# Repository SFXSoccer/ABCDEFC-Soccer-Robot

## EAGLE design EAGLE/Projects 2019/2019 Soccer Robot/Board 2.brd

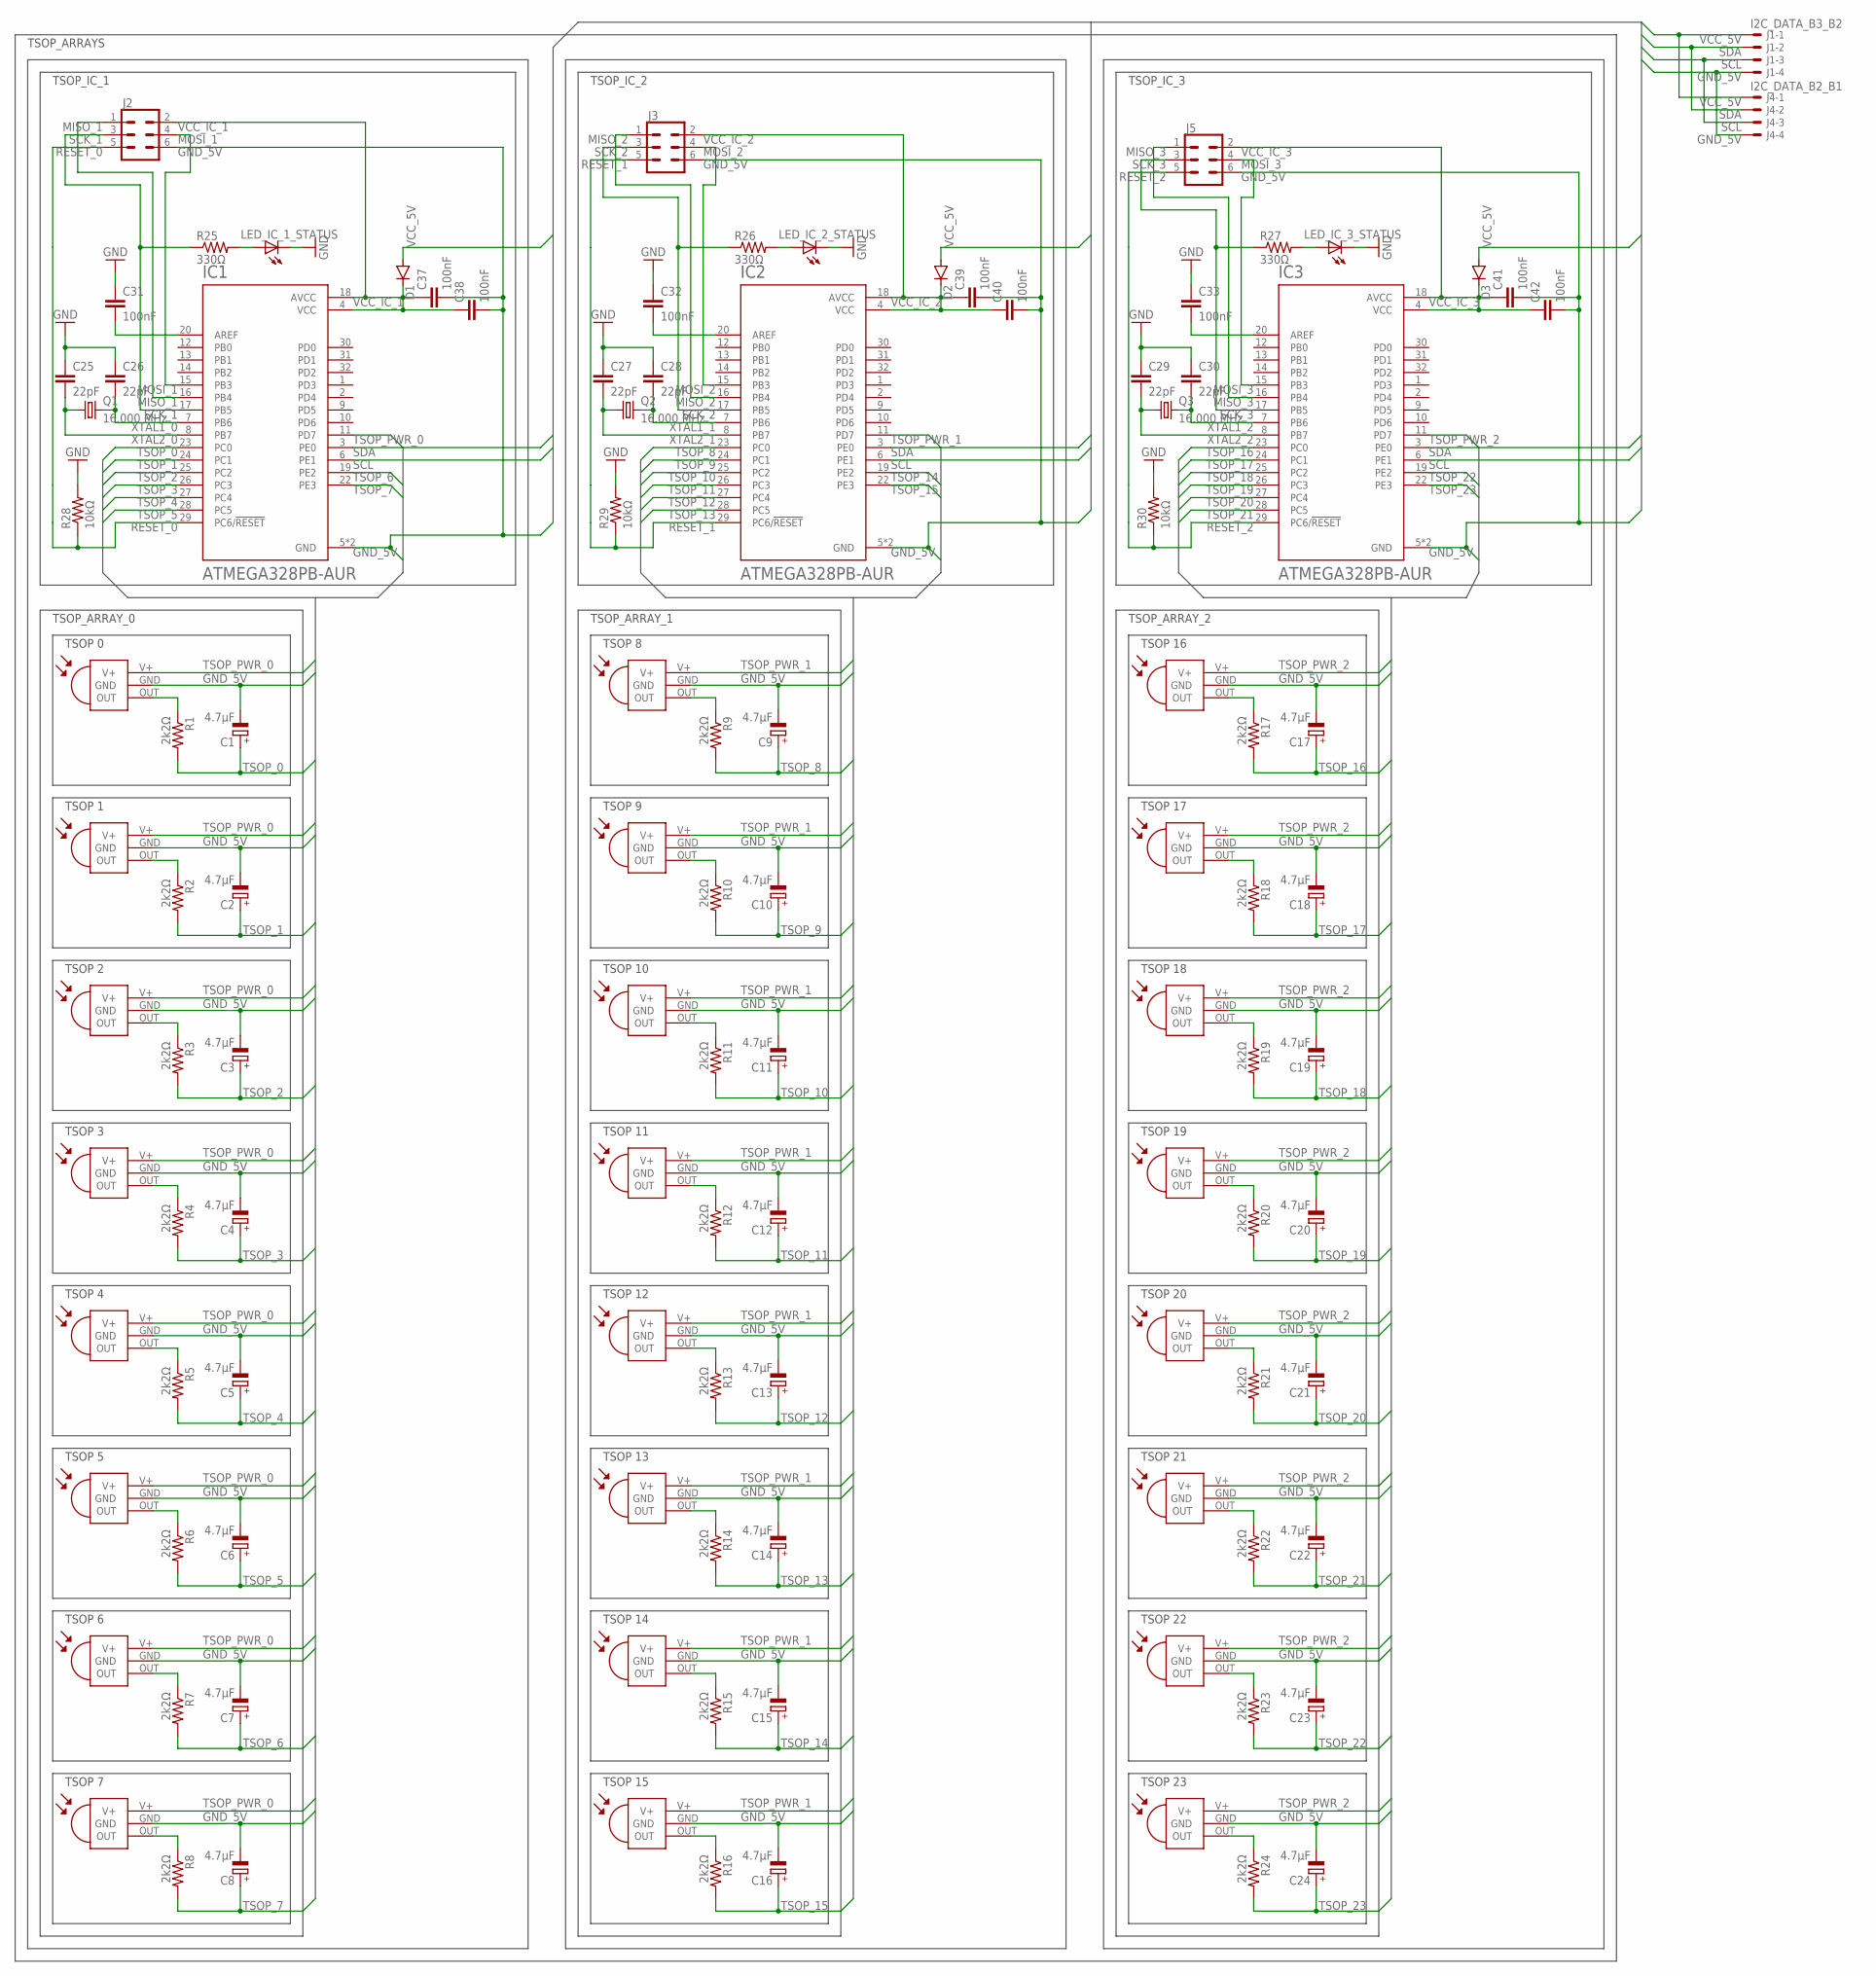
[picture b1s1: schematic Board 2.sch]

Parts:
C1, C2, C3, C4, C5, C6, C7, C8, C9, C10, C11, C12, C13, C14, C15, C16, C17, C18, C19, C20, C21, C22, C23, C24: 4.7µF; E2-5
C25, C26, C27, C28, C29, C30: 22pF; C050-024X044
C31, C32, C33, C37, C38, C39, C40, C41, C42: 100nF; C050-024X044
D1, D2, D3: 1N4148DO35-7; DO35-7
IC1, IC2, IC3: ATMEGA328PB-AUR; QFP80P900X900X120-32N
J1: I2C_DATA_B3_B2; 6410-04
J2, J3, J5: CONN_03X2SHROUD; 2X3-SHROUDED
J4: I2C_DATA_B2_B1; 6410-04
LED_IC_1_STATUS, LED_IC_2_STATUS, LED_IC_3_STATUS: LEDP-LCC-2; P-LCC-2
Q1, Q2, Q3: 16.000 MHz; HC49U-V
R1, R2, R3, R4, R5, R6, R7, R8, R9, R10, R11, R12, R13, R14, R15, R16, R17, R18, R19, R20, R21, R22, R23, R24: 2k2Ω; 0207/10
R25, R26, R27: 330Ω; 0207/10
R28, R29, R30: 10kΩ; 0207/10
TSOP_1, TSOP_2, TSOP_3, TSOP_4, TSOP_5, TSOP_6, TSOP_7, TSOP_8, TSOP_9, TSOP_10, TSOP_11, TSOP_12, TSOP_13, TSOP_14, TSOP_15, TSOP_16, TSOP_17, TSOP_18, TSOP_19, TSOP_20, TSOP_21, TSOP_22, TSOP_23, TSOP_24: TSOP14340; TSOP143XX

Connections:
GND_5V: C1.-, C2.-, C3.-, C4.-, C5.-, C6.-, C7.-, C8.-, C9.-, C10.-, C11.-, C12.-, C13.-, C14.-, C15.-, C16.-, C17.-, C18.-, C19.-, C20.-, C21.-, C22.-, C23.-, C24.-, C25.1, C26.1, C27.1, C28.1, C29.1, C30.1, C31.1, C32.1, C33.1, C37.2, C38.2, C39.2, C40.2, C41.2, C42.2, IC1.5 (GND), IC1.21 (GND), IC2.5 (GND), IC2.21 (GND), IC3.5 (GND), IC3.21 (GND), J1.4, J2.6, J3.6, J4.4, J5.6, LED_IC_1_STATUS.C, LED_IC_2_STATUS.C, LED_IC_3_STATUS.C, R28.2, R29.2, R30.2, TSOP_1.GND, TSOP_2.GND, TSOP_3.GND, TSOP_4.GND, TSOP_5.GND, TSOP_6.GND, TSOP_7.GND, TSOP_8.GND, TSOP_9.GND, TSOP_10.GND, TSOP_11.GND, TSOP_12.GND, TSOP_13.GND, TSOP_14.GND, TSOP_15.GND, TSOP_16.GND, TSOP_17.GND, TSOP_18.GND, TSOP_19.GND, TSOP_20.GND, TSOP_21.GND, TSOP_22.GND, TSOP_23.GND, TSOP_24.GND
MISO_1: IC1.16 (PB4), J2.1
MISO_2: IC2.16 (PB4), J3.1
MISO_3: IC3.16 (PB4), J5.1
MOSI_1: IC1.15 (PB3), J2.4
MOSI_2: IC2.15 (PB3), J3.4
MOSI_3: IC3.15 (PB3), J5.4
unnamed: R1.1, TSOP_1.OUT
unnamed: R2.1, TSOP_2.OUT
unnamed: R3.1, TSOP_3.OUT
unnamed: R4.1, TSOP_4.OUT
unnamed: R5.1, TSOP_5.OUT
unnamed: R6.1, TSOP_6.OUT
unnamed: R7.1, TSOP_7.OUT
unnamed: R8.1, TSOP_8.OUT
unnamed: R9.1, TSOP_9.OUT
unnamed: R10.1, TSOP_10.OUT
unnamed: R11.1, TSOP_11.OUT
unnamed: R12.1, TSOP_12.OUT
unnamed: R13.1, TSOP_13.OUT
unnamed: R14.1, TSOP_14.OUT
unnamed: R15.1, TSOP_15.OUT
unnamed: R16.1, TSOP_16.OUT
unnamed: R17.1, TSOP_17.OUT
unnamed: R18.1, TSOP_18.OUT
unnamed: R19.1, TSOP_19.OUT
unnamed: R20.1, TSOP_20.OUT
unnamed: R21.1, TSOP_21.OUT
unnamed: R22.1, TSOP_22.OUT
unnamed: R23.1, TSOP_23.OUT
unnamed: R24.1, TSOP_24.OUT
unnamed: LED_IC_1_STATUS.A, R25.2
unnamed: C31.2, IC1.20 (AREF)
unnamed: LED_IC_2_STATUS.A, R26.2
unnamed: C32.2, IC2.20 (AREF)
unnamed: LED_IC_3_STATUS.A, R27.2
unnamed: C33.2, IC3.20 (AREF)
RESET_0: IC1.29 (PC6/!RESET), J2.5, R28.1
RESET_1: IC2.29 (PC6/!RESET), J3.5, R29.1
RESET_2: IC3.29 (PC6/!RESET), J5.5, R30.1
SCK_1: IC1.17 (PB5), J2.3, R25.1
SCK_2: IC2.17 (PB5), J3.3, R26.1
SCK_3: IC3.17 (PB5), J5.3, R27.1
SCL: IC1.6 (PE1), IC2.6 (PE1), IC3.6 (PE1), J1.3, J4.3
SDA: IC1.3 (PE0), IC2.3 (PE0), IC3.3 (PE0), J1.2, J4.2
TSOP_0: C1.+, IC1.23 (PC0), R1.2
TSOP_1: C2.+, IC1.24 (PC1), R2.2
TSOP_2: C3.+, IC1.25 (PC2), R3.2
TSOP_3: C4.+, IC1.26 (PC3), R4.2
TSOP_4: C5.+, IC1.27 (PC4), R5.2
TSOP_5: C6.+, IC1.28 (PC5), R6.2
TSOP_6: C7.+, IC1.19 (PE2), R7.2
TSOP_7: C8.+, IC1.22 (PE3), R8.2
TSOP_8: C9.+, IC2.23 (PC0), R9.2
TSOP_9: C10.+, IC2.24 (PC1), R10.2
TSOP_10: C11.+, IC2.25 (PC2), R11.2
TSOP_11: C12.+, IC2.26 (PC3), R12.2
TSOP_12: C13.+, IC2.27 (PC4), R13.2
TSOP_13: C14.+, IC2.28 (PC5), R14.2
TSOP_14: C15.+, IC2.19 (PE2), R15.2
TSOP_15: C16.+, IC2.22 (PE3), R16.2
TSOP_16: C17.+, IC3.23 (PC0), R17.2
TSOP_17: C18.+, IC3.24 (PC1), R18.2
TSOP_18: C19.+, IC3.25 (PC2), R19.2
TSOP_19: C20.+, IC3.26 (PC3), R20.2
TSOP_20: C21.+, IC3.27 (PC4), R21.2
TSOP_21: C22.+, IC3.28 (PC5), R22.2
TSOP_22: C23.+, IC3.19 (PE2), R23.2
TSOP_23: C24.+, IC3.22 (PE3), R24.2
TSOP_PWR_0: IC1.11 (PD7), TSOP_1.V+, TSOP_2.V+, TSOP_3.V+, TSOP_4.V+, TSOP_5.V+, TSOP_6.V+, TSOP_7.V+, TSOP_8.V+
TSOP_PWR_1: IC2.11 (PD7), TSOP_9.V+, TSOP_10.V+, TSOP_11.V+, TSOP_12.V+, TSOP_13.V+, TSOP_14.V+, TSOP_15.V+, TSOP_16.V+
TSOP_PWR_2: IC3.11 (PD7), TSOP_17.V+, TSOP_18.V+, TSOP_19.V+, TSOP_20.V+, TSOP_21.V+, TSOP_22.V+, TSOP_23.V+, TSOP_24.V+
VCC_5V: D1.A, D2.A, D3.A, J1.1, J4.1
VCC_IC_1: C37.1, C38.1, D1.C, IC1.4 (VCC), IC1.18 (AVCC), J2.2
VCC_IC_2: C39.1, C40.1, D2.C, IC2.4 (VCC), IC2.18 (AVCC), J3.2
VCC_IC_3: C41.1, C42.1, D3.C, IC3.4 (VCC), IC3.18 (AVCC), J5.2
XTAL1_0: C26.2, IC1.7 (PB6), Q1.2
XTAL1_1: C28.2, IC2.7 (PB6), Q2.2
XTAL1_2: C30.2, IC3.7 (PB6), Q3.2
XTAL2_0: C25.2, IC1.8 (PB7), Q1.1
XTAL2_1: C27.2, IC2.8 (PB7), Q2.1
XTAL2_2: C29.2, IC3.8 (PB7), Q3.1

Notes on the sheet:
TSOP 0
TSOP 1
TSOP 2
TSOP 3
TSOP 4
TSOP 5
TSOP 6
TSOP 7
TSOP 8
TSOP 9
TSOP 10
TSOP 11
TSOP 12
TSOP 13
TSOP 14
TSOP 15
TSOP 16
TSOP 17
TSOP 18
TSOP 19
TSOP 20
TSOP 21
TSOP 22
TSOP 23
TSOP_IC_1
TSOP_IC_2
TSOP_IC_3
TSOP_ARRAY_0
TSOP_ARRAY_1
TSOP_ARRAY_2
TSOP_ARRAYS

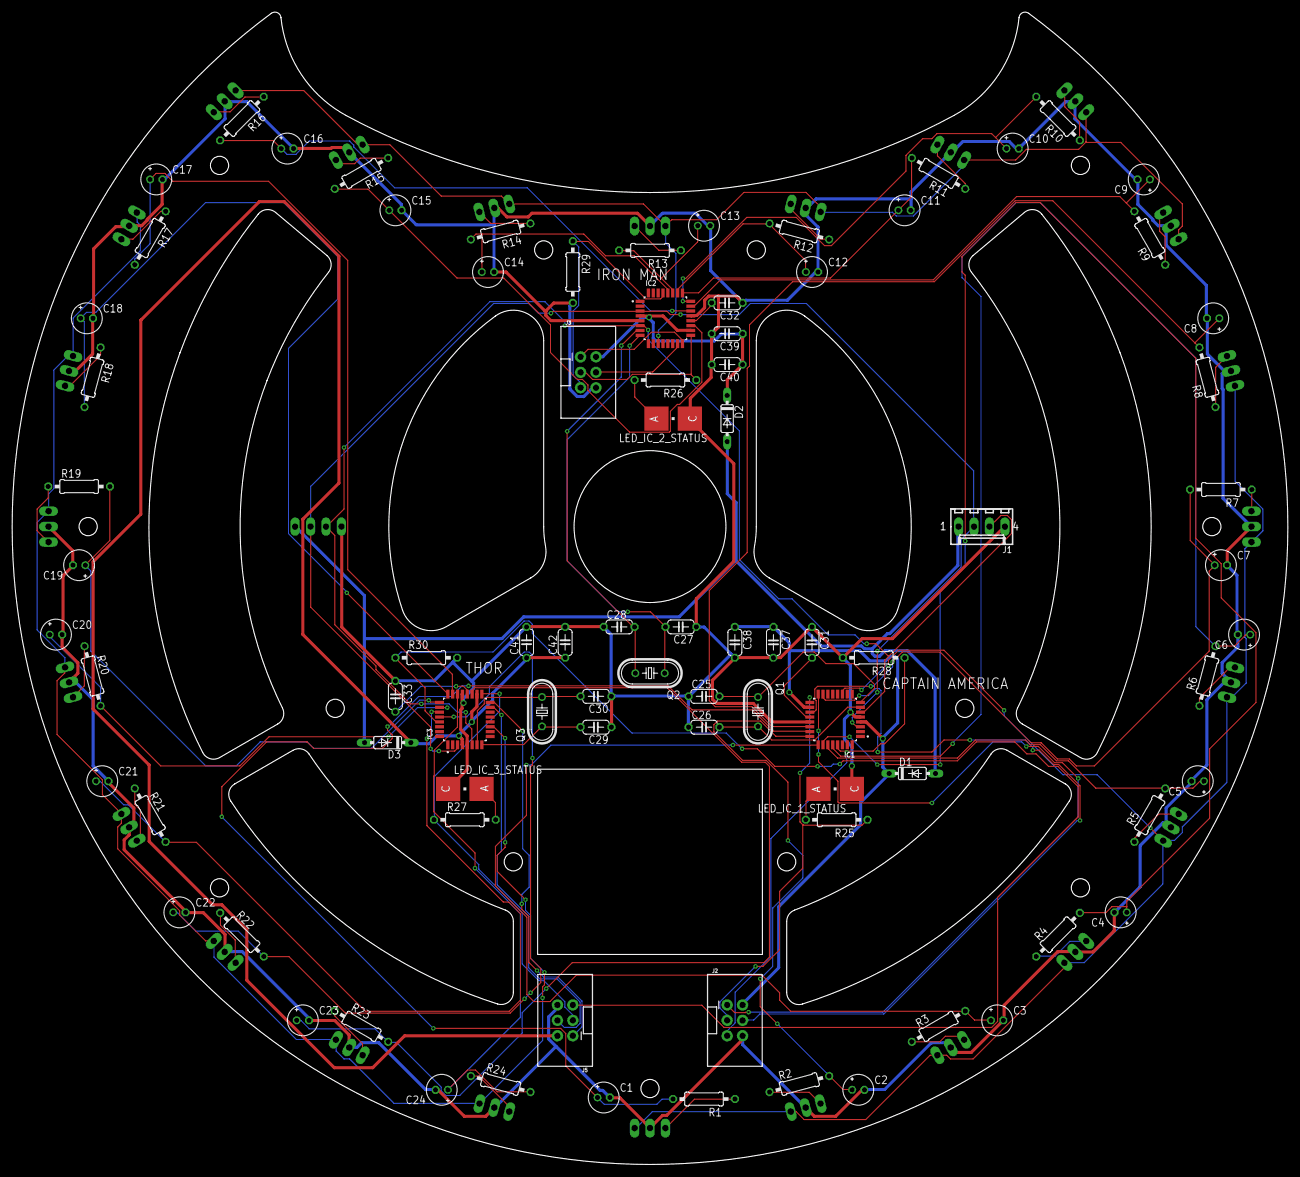
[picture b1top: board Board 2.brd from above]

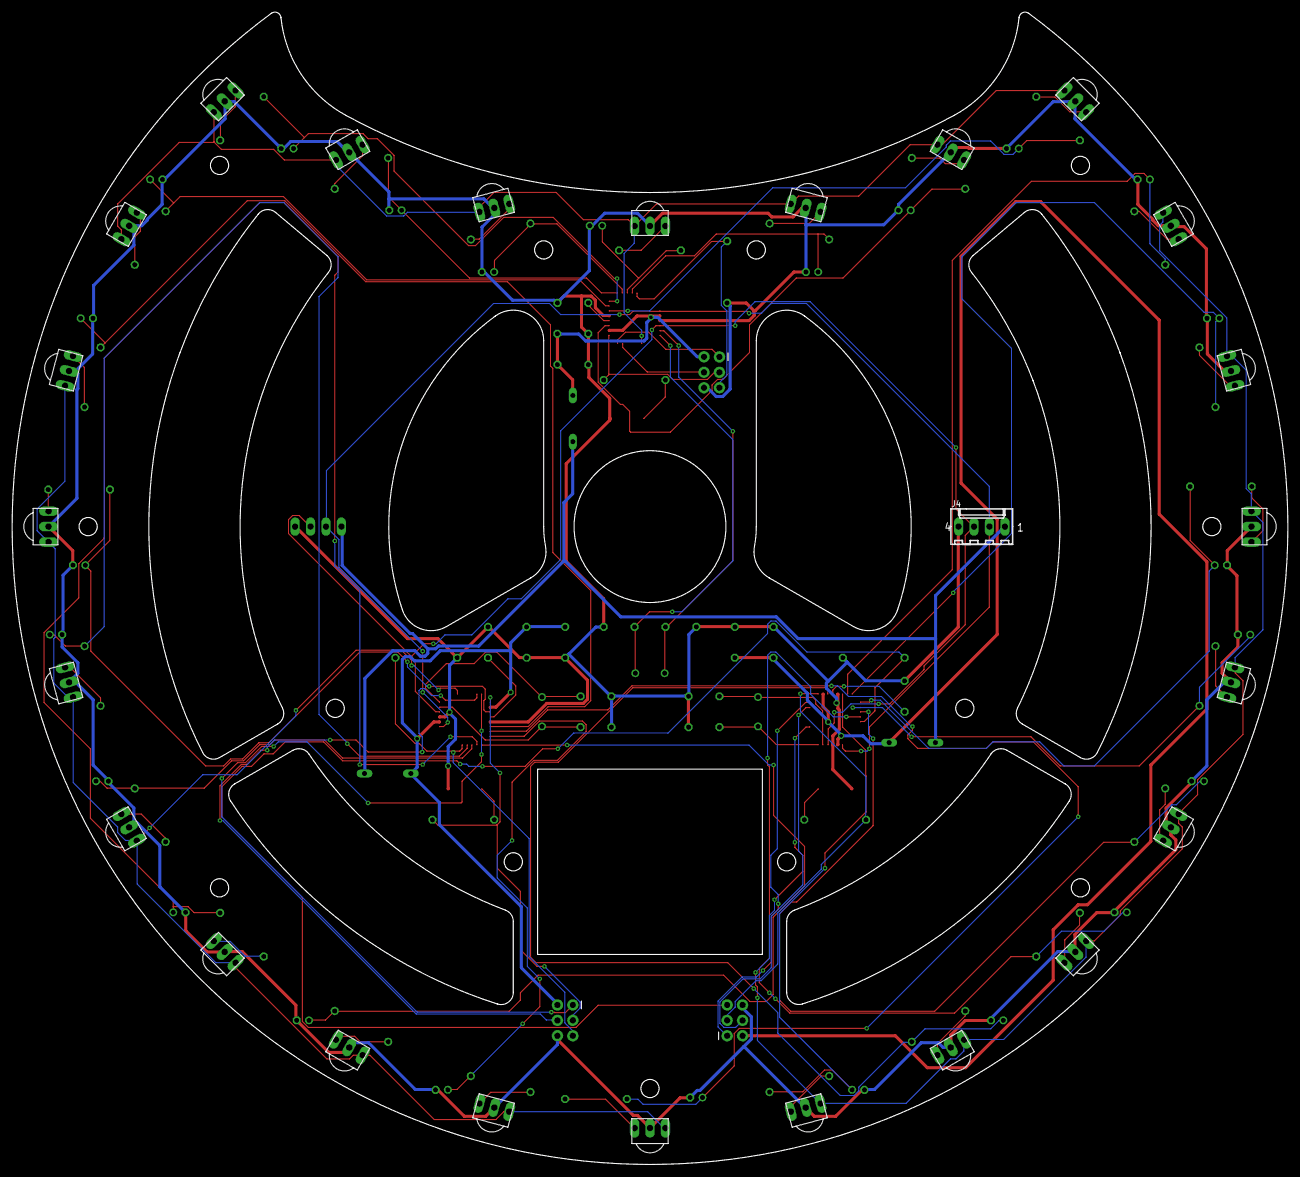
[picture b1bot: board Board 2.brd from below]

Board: 2 copper layers, 210.0 x 189.7 mm, 110 parts (25 on the bottom side), 82 nets.

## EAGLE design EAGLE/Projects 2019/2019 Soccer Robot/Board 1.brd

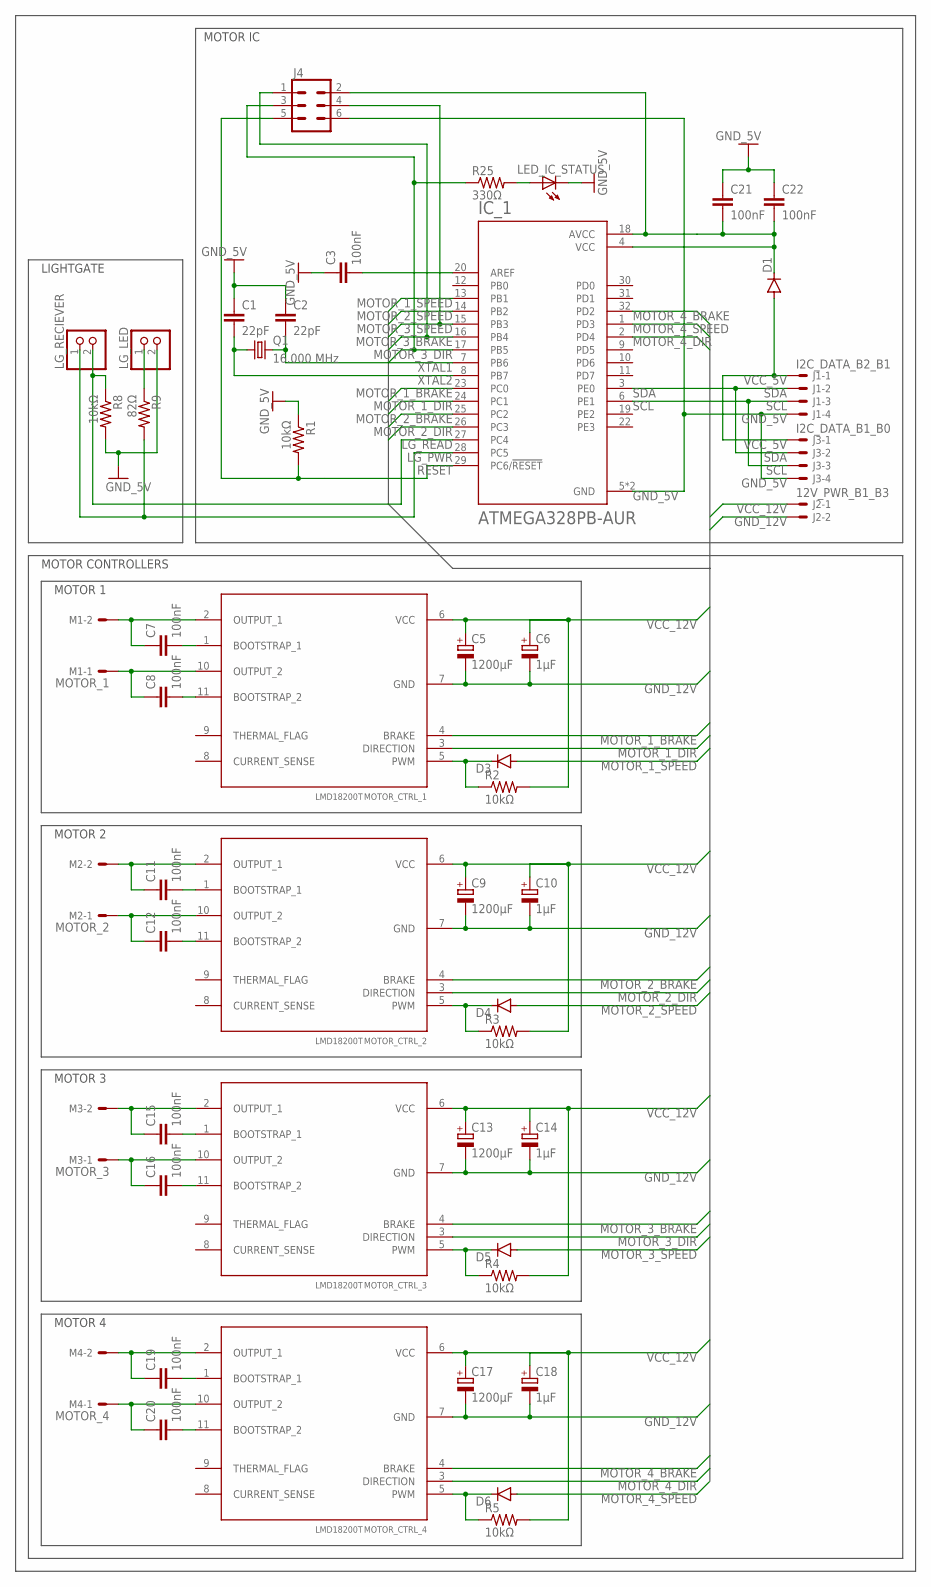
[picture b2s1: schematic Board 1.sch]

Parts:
C1, C2: 22pF; C050-024X044
C3, C7, C8, C11, C12, C15, C16, C19, C20, C21, C22: 100nF; C050-024X044
C5, C9, C13, C17: 1200µF; E5-13
C6, C10, C14, C18: 1μF; E2-5
D1, D3, D4, D5, D6: 1N4148DO35-7; DO35-7
IC_1: ATMEGA328PB-AUR; QFP80P900X900X120-32N
J1: I2C_DATA_B2_B1; 6410-04
J2: 12V_PWR_B1_B3; 6410-02
J3: I2C_DATA_B1_B0; 6410-04
J4: CONN_03X2SHROUD; 2X3-SHROUDED
LED_IC_STATUS: LEDP-LCC-2; P-LCC-2
LG_LED: PINHD-1X2; 1X02
LG_RECIEVER: PINHD-1X2; 1X02
M1: MOTOR_1; 6410-02
M2: MOTOR_2; 6410-02
M3: MOTOR_3; 6410-02
M4: MOTOR_4; 6410-02
MOTOR_CTRL_1, MOTOR_CTRL_2, MOTOR_CTRL_3, MOTOR_CTRL_4: LMD18200T; TO-220-11
Q1: 16.000 MHz; HC49U-V
R1, R2, R3, R4, R5, R8: 10kΩ; 0207/10
R9: 82Ω; 0207/10
R25: 330Ω; 0207/10

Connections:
GND_5V: C1.1, C2.1, C3.1, C21.1, C22.1, IC_1.5 (GND), IC_1.21 (GND), J1.4, J3.4, J4.6, LED_IC_STATUS.C, LG_LED.2, R1.1, R8.2
GND_12V: C5.-, C6.-, C9.-, C10.-, C13.-, C14.-, C17.-, C18.-, J2.2, MOTOR_CTRL_1.7 (GND), MOTOR_CTRL_2.7 (GND), MOTOR_CTRL_3.7 (GND), MOTOR_CTRL_4.7 (GND)
LG_PWR: IC_1.28 (PC5), LG_RECIEVER.1, R9.2
LG_READ: IC_1.27 (PC4), LG_RECIEVER.2, R8.1
MOTOR_1_BRAKE: IC_1.23 (PC0), MOTOR_CTRL_1.4 (BRAKE)
MOTOR_1_DIR: IC_1.24 (PC1), MOTOR_CTRL_1.3 (DIRECTION)
MOTOR_1_SPEED: D3.A, IC_1.13 (PB1)
MOTOR_2_BRAKE: IC_1.25 (PC2), MOTOR_CTRL_2.4 (BRAKE)
MOTOR_2_DIR: IC_1.26 (PC3), MOTOR_CTRL_2.3 (DIRECTION)
MOTOR_2_SPEED: D4.A, IC_1.14 (PB2)
MOTOR_3_BRAKE: IC_1.16 (PB4), J4.1, MOTOR_CTRL_3.4 (BRAKE)
MOTOR_3_DIR: IC_1.17 (PB5), J4.3, MOTOR_CTRL_3.3 (DIRECTION), R25.1
MOTOR_3_SPEED: D5.A, IC_1.15 (PB3), J4.4
MOTOR_4_BRAKE: IC_1.32 (PD2), MOTOR_CTRL_4.4 (BRAKE)
MOTOR_4_DIR: IC_1.2 (PD4), MOTOR_CTRL_4.3 (DIRECTION)
MOTOR_4_SPEED: D6.A, IC_1.1 (PD3)
unnamed: C3.2, IC_1.20 (AREF)
unnamed: LG_LED.1, R9.1
unnamed: LED_IC_STATUS.A, R25.2
unnamed: D3.C, MOTOR_CTRL_1.5 (PWM), R2.1
unnamed: C7.1, M1.2, MOTOR_CTRL_1.2 (OUTPUT_1)
unnamed: C21.2, C22.2, D1.C, IC_1.4 (VCC), IC_1.18 (AVCC), J4.2
unnamed: C8.1, M1.1, MOTOR_CTRL_1.10 (OUTPUT_2)
unnamed: C8.2, MOTOR_CTRL_1.11 (BOOTSTRAP_2)
unnamed: C7.2, MOTOR_CTRL_1.1 (BOOTSTRAP_1)
unnamed: D4.C, MOTOR_CTRL_2.5 (PWM), R3.1
unnamed: C11.1, M2.2, MOTOR_CTRL_2.2 (OUTPUT_1)
unnamed: C12.1, M2.1, MOTOR_CTRL_2.10 (OUTPUT_2)
unnamed: C12.2, MOTOR_CTRL_2.11 (BOOTSTRAP_2)
unnamed: C11.2, MOTOR_CTRL_2.1 (BOOTSTRAP_1)
unnamed: D5.C, MOTOR_CTRL_3.5 (PWM), R4.1
unnamed: C15.1, M3.2, MOTOR_CTRL_3.2 (OUTPUT_1)
unnamed: C16.1, M3.1, MOTOR_CTRL_3.10 (OUTPUT_2)
unnamed: C16.2, MOTOR_CTRL_3.11 (BOOTSTRAP_2)
unnamed: C15.2, MOTOR_CTRL_3.1 (BOOTSTRAP_1)
unnamed: D6.C, MOTOR_CTRL_4.5 (PWM), R5.1
unnamed: C19.1, M4.2, MOTOR_CTRL_4.2 (OUTPUT_1)
unnamed: C20.1, M4.1, MOTOR_CTRL_4.10 (OUTPUT_2)
unnamed: C20.2, MOTOR_CTRL_4.11 (BOOTSTRAP_2)
unnamed: C19.2, MOTOR_CTRL_4.1 (BOOTSTRAP_1)
RESET: IC_1.29 (PC6/!RESET), J4.5, R1.2
SCL: IC_1.6 (PE1), J1.3, J3.3
SDA: IC_1.3 (PE0), J1.2, J3.2
VCC_5V: D1.A, J1.1, J3.1
VCC_12V: C5.+, C6.+, C9.+, C10.+, C13.+, C14.+, C17.+, C18.+, J2.1, MOTOR_CTRL_1.6 (VCC), MOTOR_CTRL_2.6 (VCC), MOTOR_CTRL_3.6 (VCC), MOTOR_CTRL_4.6 (VCC), R2.2, R3.2, R4.2, R5.2
XTAL1: C2.2, IC_1.7 (PB6), Q1.2
XTAL2: C1.2, IC_1.8 (PB7), Q1.1

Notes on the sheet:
MOTOR 1
MOTOR 2
MOTOR 3
MOTOR 4
MOTOR CONTROLLERS
MOTOR IC
LIGHTGATE

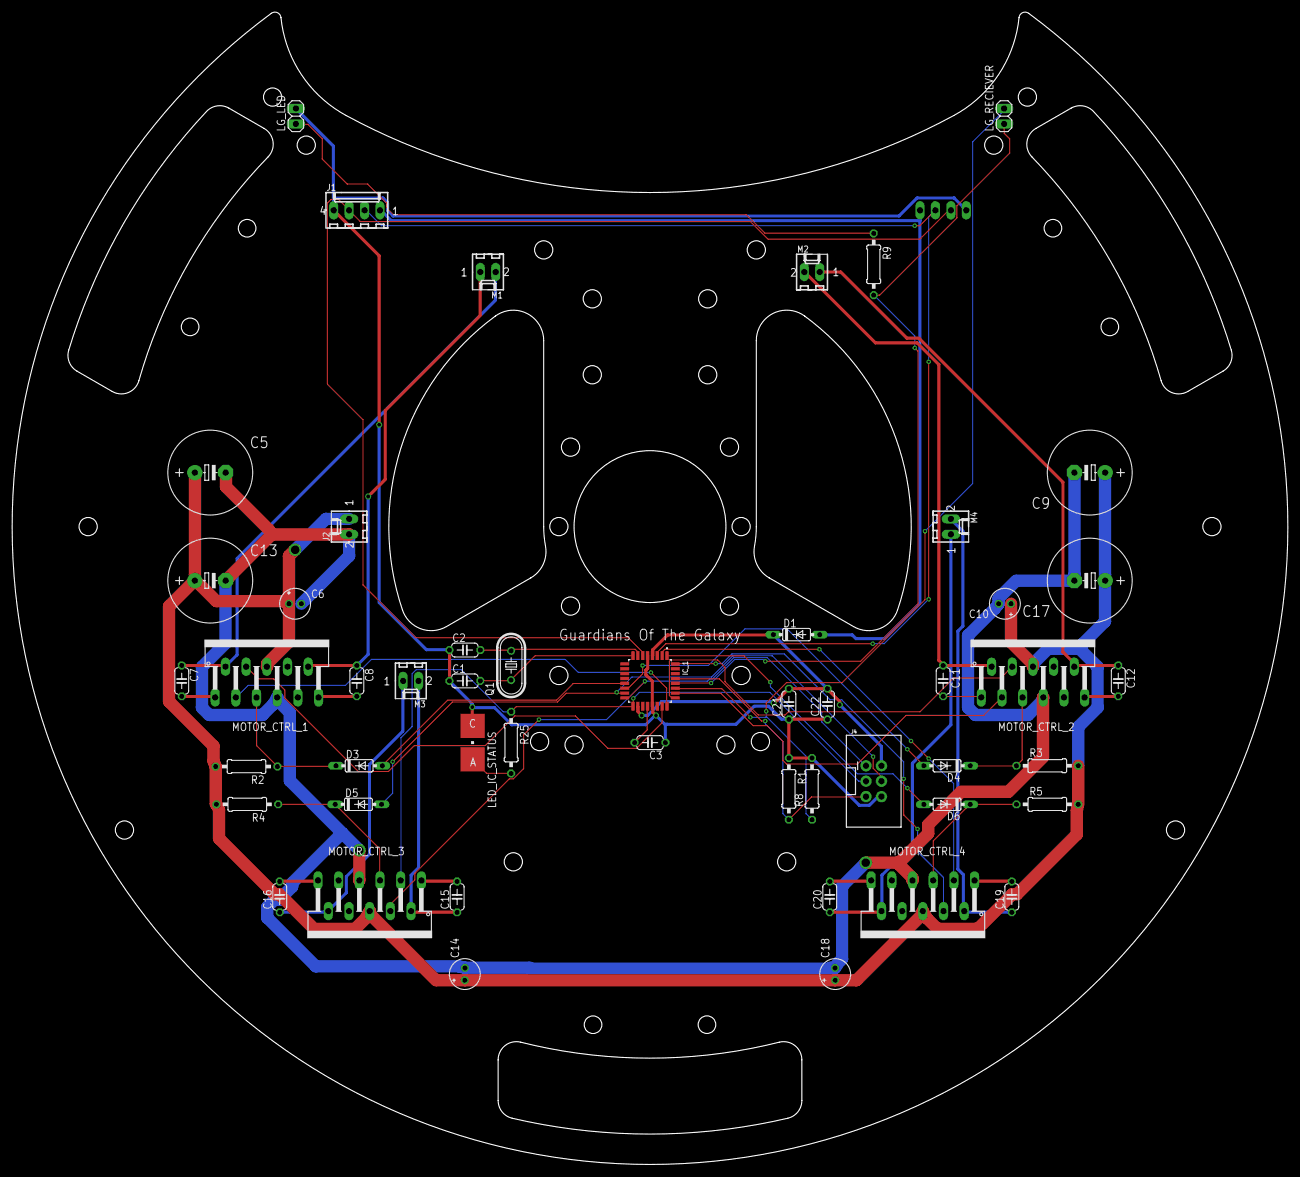
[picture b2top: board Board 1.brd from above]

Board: 2 copper layers, 210.0 x 189.7 mm, 51 parts (1 on the bottom side), 47 nets.

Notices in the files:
parts and their libraries:
SparkFun-Clocks: Licensing: Creative Commons ShareAlike 4.0 International - https://creativecommons.org/licenses/by-sa/4.0
